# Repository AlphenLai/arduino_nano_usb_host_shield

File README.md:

# arduino_nano_usb_host_shield
An USB host shield for Arduino Nano, built from a mini USB host shield

This project creates an interface to combine easy accessed Arduino Nano and Arduino Mini USB Host Shield. This can be meaningless as USB Host Shield for Arduino Uno is everywhere on the market. If size doesn't matter, that would be a far easier option.

## Hardware

### BOM

| Reference   | Quantity | Value           | Footprint                  |
| ----------- | -------- | --------------- | -------------------------- | 
| A1          | 1        | Arduino_Nano    |                            |
| D1 D2 D3 D4 | 4        | LED             | LED_0603                   |
| 5V_share    | 1        | Conn_01x02_Male | Connector_PinHeader_2.54mm |
| Output      | 1        | Conn_01x09_Male | Connector_PinHeader_2.54mm |
| Host_Shield | 2        | Conn_01x02_Male | Connector_PinHeader_2.54mm |
| Host_Shield | 2        | Conn_01x04_Male | Connector_PinHeader_2.54mm |
| Nano pin    | 13       | Conn_01x13_Male | Connector_PinHeader_2.54mm |
| R1 R2 R3 R4 | 4        | 220             | R_0805                     |
| R5 R6 R7 R8 | 4        | 10k             | R_0805                     |
| SW1         | 1        | SW_DIP_x04      | SW_DIP_SPSTx04_Slide       |

### Preview

### Pins

#### Assignment

| Pin  | Usage     |
| ---- | --------- |
| A0   | IO        |
| A1   | IO        |
| 0	   | Serial RX |
| 1    | Serial TX |
| A2   | PWM out   |
| 4    | Switch 1  |
| 5    | Switch 2  |
| 6    | Switch 3  |
| 7    | Switch 4  |
| 8    | LED 1     |
| 9    | LED 2     |
| A2   | LED 3     |
| A3   | LED 4     |

There are 4 programmable LEDs and 4 switches on the board, which allows multiple purposes.

A Serial, a PWM pin, and 2 IO pins are routed to usable headers. PWM pins is for PPM output, and the IO pins are for software serial.

If you are happy to power everything with single source, put a jumper on the header below:

Otherwise, use the headers to provide private power to Arduino Nano and USB device respectively.

#### Soldering Tips

The stock Arduino Mini USB Host Shield uses 3.3V from Arduino Mini to power up the USB device. Usually this is not enough. Clone boards removed a VBUS jumper so there is no voltage selection, cut the trace and use middleman board to supply 5V to USB device.

Solder headers to labeled pins.

Soldering both boards to the middleman board would cause huge pain if any repairing is needed later. Consider using socket or pogo pin for Arduino's side. Reference dimensions:

with A=5, B=1.5, C=3.5, E=2, F=0.8, 13pin, plastic housing interval 2.54, width 2.55, height 2.5

#### Housing

The 3D printable housing is designed for pogo pins or headers. If you have the top headers on Arduino or using socket for connection, the housing will be too small.

There are some buckles to press the pogo pins continuously, as the screws are too far away to keep adding pressing, due to lack of space. Remove the buckles if you soldered everything together with headers.

## Software

Uses USB_Host_Shield_2.0 library by felis

https://github.com/felis/USB_Host_Shield_2.0

It should work on the Nano.

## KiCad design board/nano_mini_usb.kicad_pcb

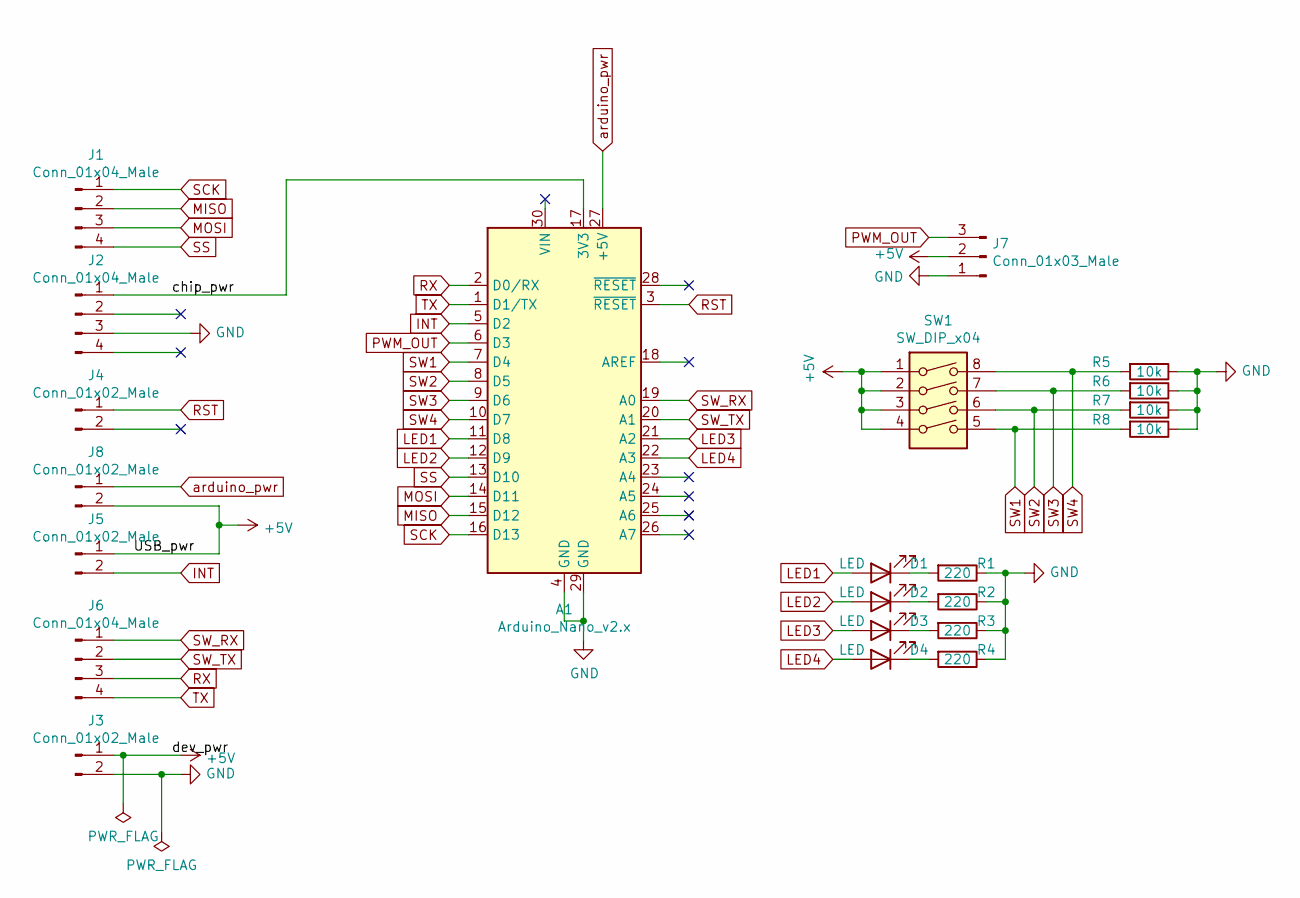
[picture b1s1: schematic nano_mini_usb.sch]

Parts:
A1: Arduino_Nano_v2.x; Arduino_Nano
D1, D2, D3, D4: LED; LED_0603_1608Metric_Pad1.05x0.95mm_HandSolder
J1, J2, J6: Conn_01x04_Male; PinHeader_1x04_P2.54mm_Vertical
J3, J4, J5, J8: Conn_01x02_Male; PinHeader_1x02_P2.54mm_Vertical
J7: Conn_01x03_Male; PinHeader_1x03_P2.54mm_Vertical
R1, R2, R3, R4: 220; R_0805_2012Metric_Pad1.20x1.40mm_HandSolder
R5, R6, R7, R8: 10k; R_0805_2012Metric_Pad1.20x1.40mm_HandSolder
SW1: SW_DIP_x04; SW_DIP_SPSTx04_Slide_9.78x12.34mm_W7.62mm_P2.54mm

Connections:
+5V: J3.1, J5.1, J7.2, J8.2, SW1.1, SW1.2, SW1.3, SW1.4
/chip_pwr: A1.17 (3V3), J2.1
GND: A1.4 (GND), A1.29 (GND), J2.3, J3.2, J7.1, R1.1, R2.1, R3.1, R4.1, R5.1, R6.1, R7.1, R8.1
INT: A1.5 (D2), J5.2
LED1: A1.11 (D8), D1.2 (A)
LED2: A1.12 (D9), D2.2 (A)
LED3: A1.21 (A2), D3.2 (A)
LED4: A1.22 (A3), D4.2 (A)
MISO: A1.15 (D12), J1.2
MOSI: A1.14 (D11), J1.3
unnamed: D1.1 (K), R1.2
unnamed: D2.1 (K), R2.2
unnamed: D3.1 (K), R3.2
unnamed: D4.1 (K), R4.2
PWM_OUT: A1.6 (D3), J7.3
RST: A1.3 (~RESET), J4.1
RX: A1.2 (D0/RX), J6.3
SCK: A1.16 (D13), J1.1
SS: A1.13 (D10), J1.4
SW1: A1.7 (D4), R8.2, SW1.5
SW2: A1.8 (D5), R7.2, SW1.6
SW3: A1.9 (D6), R6.2, SW1.7
SW4: A1.10 (D7), R5.2, SW1.8
SW_RX: A1.19 (A0), J6.1
SW_TX: A1.20 (A1), J6.2
TX: A1.1 (D1/TX), J6.4
arduino_pwr: A1.27 (+5V), J8.1

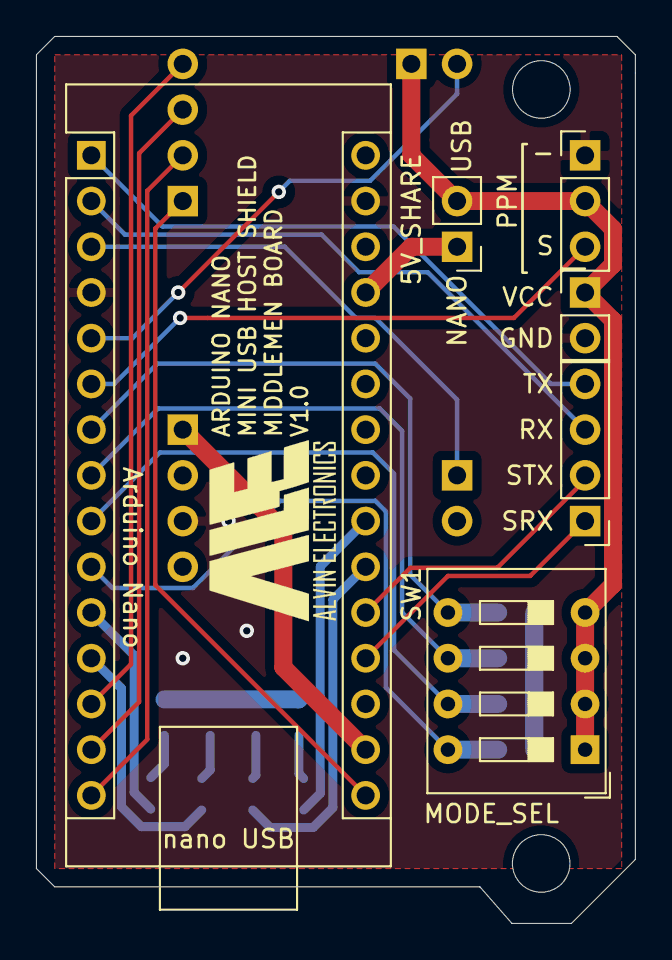
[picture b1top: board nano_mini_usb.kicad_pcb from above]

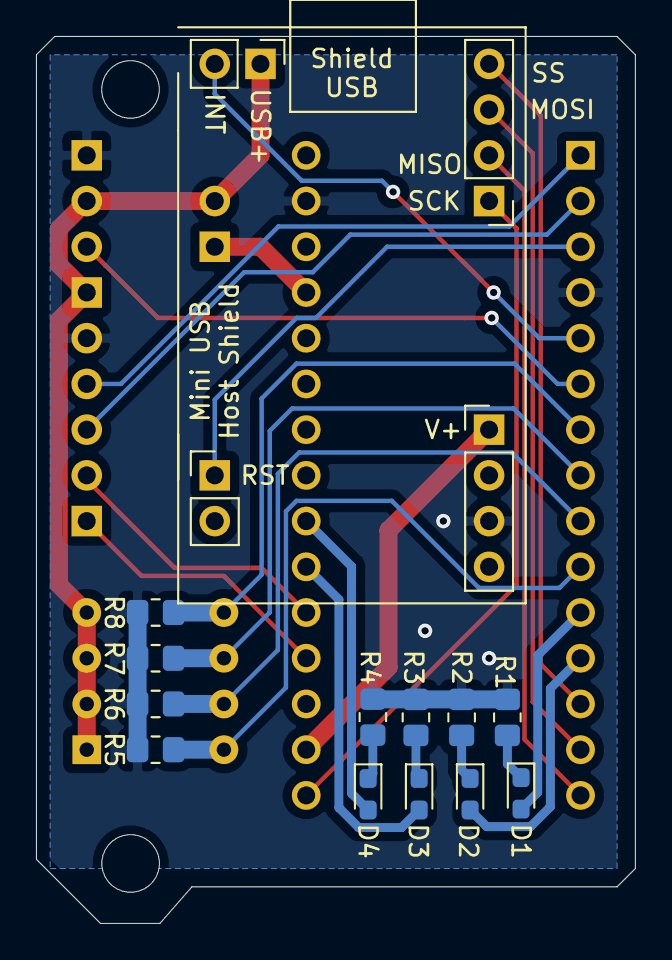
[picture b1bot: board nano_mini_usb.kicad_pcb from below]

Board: 2 copper layers, 33.3 x 49.3 mm, 22 parts (16 on the bottom side), 27 nets.

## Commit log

2021-10-31 Initial Upload
2021-11-01 Upload 3D files
2021-11-01 Update PCB. Re-route switch power to Arduino +5V
2021-11-01 Re-upload gerber
2021-11-01 Fix format
2021-11-01 Update explanation of codes
2021-11-01 Add dimension of the board
